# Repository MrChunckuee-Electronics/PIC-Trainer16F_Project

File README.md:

# PIC-Trainer16F_Project

***
Puedes seguirme en:
- [Blogspot](http://mrchunckuee.blogspot.com)
- [Instagram](https://www.instagram.com/mrchunckuee_electronics/)
- [Facebook](https://www.facebook.com/MrChunckueeElectronics)
- [Twitter](https://twitter.com/MrChunckuee)
- [YouTube](https://www.youtube.com/@MrChunckueeElectronics)

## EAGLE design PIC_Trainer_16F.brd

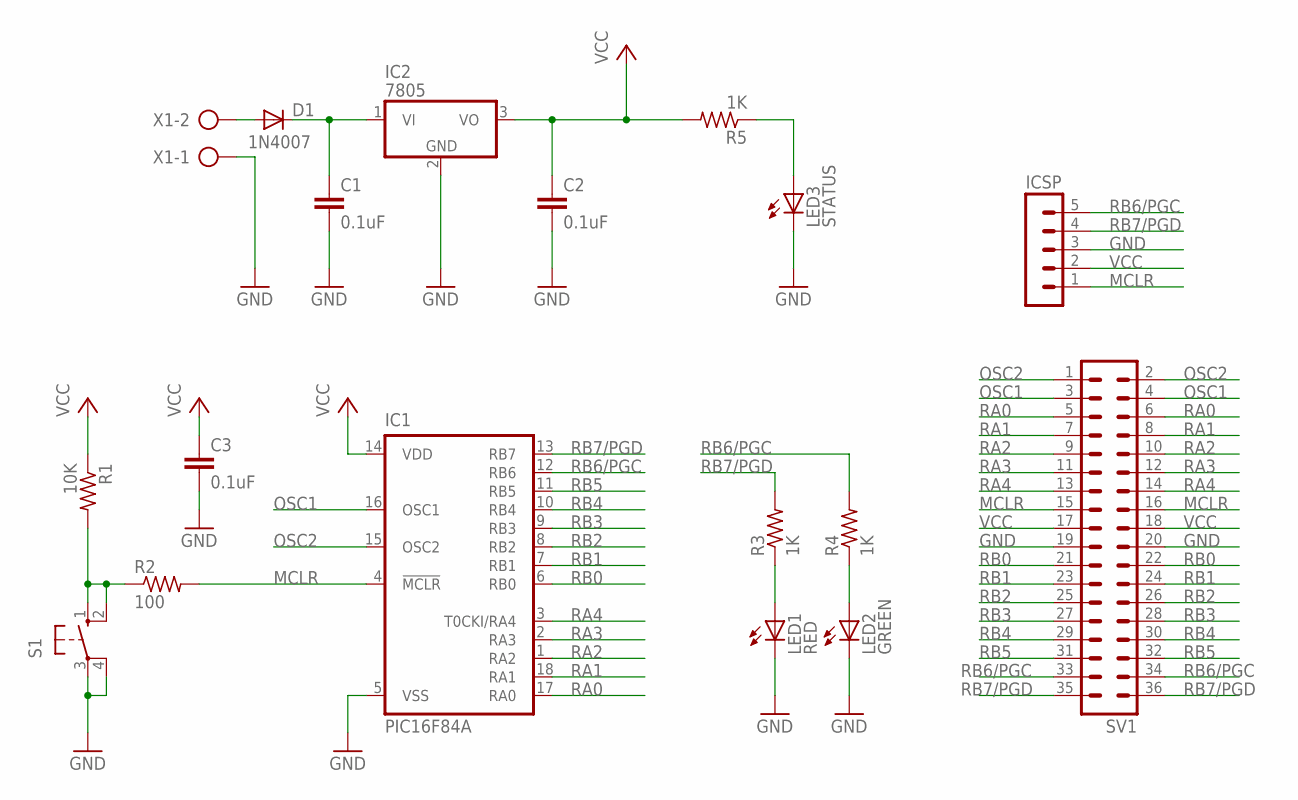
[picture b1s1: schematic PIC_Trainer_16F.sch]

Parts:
C1, C2, C3: 0.1uF; C050-025X075
D1: 1N4007; DO41-10
IC1: PIC16F84A; DIL18
IC2: 7805; TO220H
ICSP: MA05-1
LED1: RED; LED5MM
LED2: GREEN; LED5MM
LED3: STATUS; LED5MM
R1: 10K; 0207/7
R2: 100; 0207/7
R3, R4, R5: 1K; 0207/7
S1: 10-XX; B3F-10XX
SV1: MA18-2
X1: AK500/2-H

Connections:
GND: C1.2, C2.2, C3.2, IC1.5 (VSS), IC2.2 (GND), ICSP.3, LED1.K (C), LED2.K (C), LED3.K (C), S1.3, S1.4 (P1), SV1.19, SV1.20, X1.1
MCLR: IC1.4 (!MCLR), ICSP.1, R2.2, SV1.15, SV1.16
unnamed: LED3.A, R5.1
unnamed: C1.1, D1.C, IC2.1 (VI)
unnamed: D1.A, X1.2
unnamed: LED1.A, R3.1
unnamed: R1.2, R2.1, S1.1 (S), S1.2 (S1)
unnamed: LED2.A, R4.1
OSC1: IC1.16 (OSC1), SV1.3, SV1.4
OSC2: IC1.15 (OSC2), SV1.1, SV1.2
RA0: IC1.17 (RA0), SV1.5, SV1.6
RA1: IC1.18 (RA1), SV1.7, SV1.8
RA2: IC1.1 (RA2), SV1.9, SV1.10
RA3: IC1.2 (RA3), SV1.11, SV1.12
RA4: IC1.3 (T0CKI/RA4), SV1.13, SV1.14
RB0: IC1.6 (RB0), SV1.21, SV1.22
RB1: IC1.7 (RB1), SV1.23, SV1.24
RB2: IC1.8 (RB2), SV1.25, SV1.26
RB3: IC1.9 (RB3), SV1.27, SV1.28
RB4: IC1.10 (RB4), SV1.29, SV1.30
RB5: IC1.11 (RB5), SV1.31, SV1.32
RB6/PGC: IC1.12 (RB6), ICSP.5, R4.2, SV1.33, SV1.34
RB7/PGD: IC1.13 (RB7), ICSP.4, R3.2, SV1.35, SV1.36
VCC: C2.1, C3.1, IC1.14 (VDD), IC2.3 (VO), ICSP.2, R1.1, R5.2, SV1.17, SV1.18

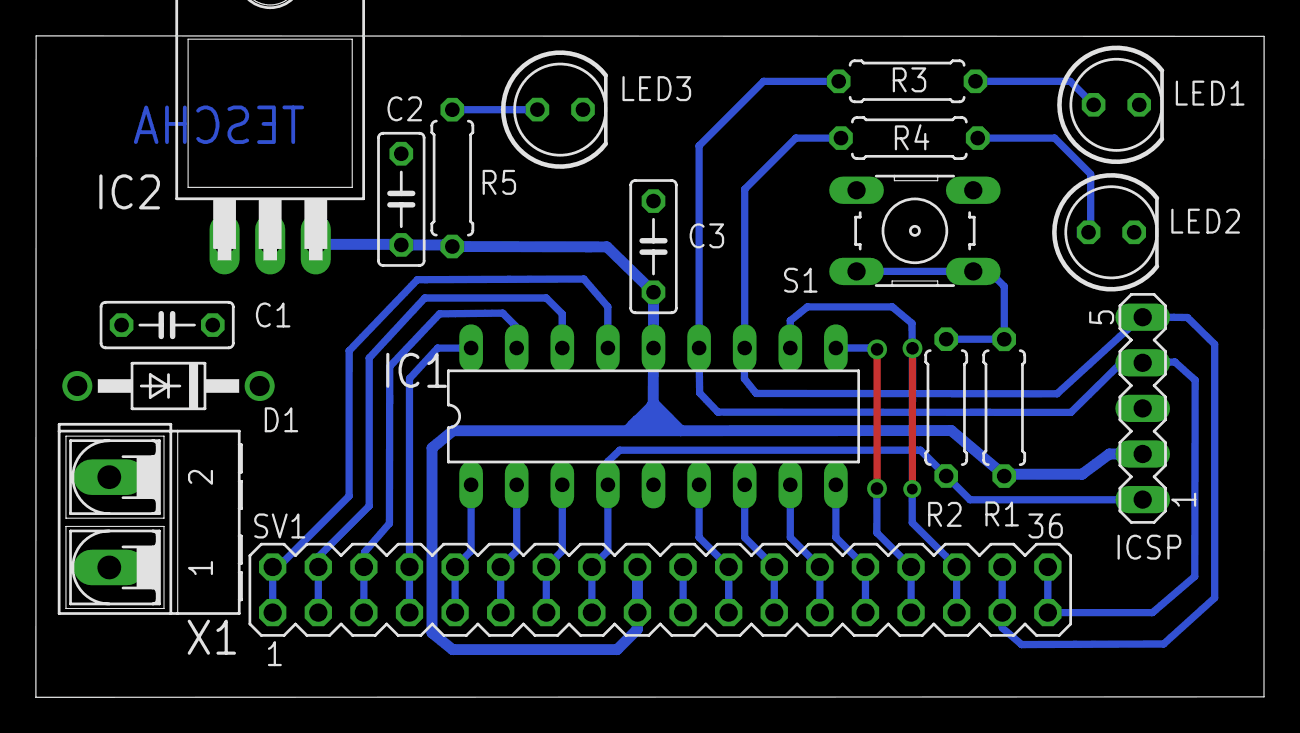
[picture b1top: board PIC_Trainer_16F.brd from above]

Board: 2 copper layers, 68.4 x 36.8 mm, 18 parts (0 on the bottom side), 24 nets.
